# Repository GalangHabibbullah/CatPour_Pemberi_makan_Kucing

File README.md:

# 🐱 **CatPour** 🐱

---
🐱CatPour🐱 - SOLUSI CERDAS PARA CATLOVERS
Pernah merasa bersalah karena lupa memberi makan kucing karena sedang bepergian jauh? Atau bingung berapa porsi makan kucing yang dibutuhkan? CatPour hadir sebagai solusi cerdas para catlovers

Bayangkan kamu pulang ke rumah setelah berlibur. Kucingmu mengeong karena sedang kelaparan karena makanan yang telah kamu siapkan sudah habis tak bersisa. Tapi tenang kejadian itu tidak akan terulang ketika CatPour hadir.

CatPour hadir untuk menyelesaikan masalah para catlovers ketika sedeang bepergian. Sekarang Catlovers tidak perlu khawatir terhadap kucing piaraanya yang kelaparan, karena Catpour memberikan makanan secara otomatis sesuai jadwal dan dalam porsi yang cukup.

---
## 🎬 Commercial Video

---
## BUKU PANDUAN
📘 [Klik di sini untuk melihat buku proyek](./ASSET/buku.pdf)

## Link simulasi Wokwi
-- https://wokwi.com/projects/432622796153693185
-- [https://github.com/GalangHabibbullah/CatPour_Pemberi_makan_Kucing/tree/fe5401d0f07f7c271f16389e5ba98aa213cf10a5/PROGRAM/Wokwi](https://github.com/GalangHabibbullah/CatPour_Pemberi_makan_Kucing/issues/2#issue-3108791988)

---

## Link Video Demo
-- [https://github.com/GalangHabibbullah/CatPour_Pemberi_makan_Kucing/tree/d1d1669227759c1687d57a3f496b5af06effbe53/PROGRAM/Demo](https://github.com/GalangHabibbullah/CatPour_Pemberi_makan_Kucing/issues/1#issue-3108780877)

---

## TINGVERS
-- https://www.thingiverse.com/thing:7054144

---

## LINK PPT PRESENTASI

---

## LINK FIGMA
https://www.figma.com/design/loQbXYYag1uOcxZlFO6y6Z/Untitled?node-id=12-356&p=f&t=XrePOnV4dfjZV4aA-0

---
## 🎯 Objectives

- Mendeteksi jumlah sisa makanan pada bak penampungan makan  
- Memberi makan sesuai dengan porsi si kucing
- Memberi makan secara otomatis sesuai dengan jadwal makan.
- Menyediakan monitoring sisa makanan secara real-time melalui UART ke komputer
---
## 🧠 LATAR BELAKANG
Mempunyai kucing piaraan merupakan kesenangan sebagian orang, sering kali juga menjadi tantangan dalam hal pemberian makan, terutama bagi orang-orang sibuk atau yang sering  bepergian. Salah satu penyebab ketidakaturan ini bisa berdampak pada kesehatan kucing

**CatPour** memberikan solusi dengan cara pemberian makan otomatis sesuai porsi makan kucing  yang dibutuhkan.

---

## 🦾 Support BY :
>- Dosen Pengampu : Akhmad Hendriawan ST., MT. (NIP.197501272002121003)<br>
>- Mata kuliah : Workshop Mikrokontroller<br>
>- Program Studi : D3 Teknik Elektronika<br>
>- Politeknik Elektronika Negeri Surabaya<br>
---
## 😎 Team Member
|      NRP      |        Nama       |        Jobdesk        |                    Akun                  |
| :-----------: |:----------------: | :-------------------: | :---------------------------------------:|
| 2123500004    | Rachmat Dhani G   | 3D Design             | [Dhani](https://github.com/rachmatdhani)
| 2123500005    | M. Ghibran K      | Hardware              | [Ghibran](https://github.com/Smolyyymokka)
| 2123500020    | Adhitya Ramadhani | UI / UX Design        | [Firman](https://github.com/adhitya161004)
| 2123500025    | Adhi Pramana R    | Programmer            | [Rama](https://github.com/Adhi-Rama)
| 2123500030    | Galang Habibbullah| Project Manager       | [Galang](https://github.com/GalangHabibbullah)
---
## 🔗 KOMPONEN 🔗 

Proyek ini mengembangkan sistem pemberian makan kucing otomatis berbasis IoT menggunakan komponen utama seperti **Arduino Uno**, **RTC (Real-Time Clock)**, **Loadcell**, dan **sensor HC-SR04**. 
| Komponen        | Fungsi                                                                                   |
|-----------------|------------------------------------------------------------------------------------------|
| **Arduino Uno** | Berfungsi sebagai mikrokontroler utama yang mengontrol sistem, komunikasi sensor, dan pengaturan pemberian makan otomatis. |
| **RTC**         | Menjaga sinkronisasi waktu untuk pemberian makan sesuai jadwal yang telah diatur.         |
| **Loadcell**    | Mengukur berat makanan di wadah makan untuk memastikan porsi makanan yang tepat.          |
| **Sensor HC-SR04** | Untuk memonitoring jumlah kesediaan ppakan dipenampungan pakan.    |
---
## Desain 3D PCB
Desain 3D VIEW KICAD

---

## Desain Schematic PCB
Desain Schematic 

---
## Desain Layout
Desain Layout PCB 

---
## Desain  PCB JADI
Hasil Cetak PCB

---
## Desain 3D Alat

---
## Desain Jadi

---
## 📊Diagram Blok
Diagram Blok Sistem.

---

## Software Tools

- [Arduino IDE](https://www.arduino.cc/en/software)
- [KiCad](https://kicad.org/)
- [Figma](https://www.figma.com/)
- [Visual Studio Code](https://code.visualstudio.com/)
---
## PRINSIP KERJA 
## Pembacaan penampungan makan
- Sensor HCSR 04 mengirim nilai jarak yang dikonversi menjadi nilai %
100 % = Penampungan Makan Full ; 0 % = Penampungan Makan Kosong
- Sensor Loadcell membaca berat pakan kucing yang keluar, apabila mencapai 20 gram maka servo akan menutup
## Pemrosesan oleh Arduino 
- Arduino  Membaca data  sensor secara berkala, Keputusan diambil untuk membuka servo atau menutup servo
## Tampilan Gui 
- GUI akan menampilkan data berat, sisa makan dan juga posisi servo

--- 
## Pengembangan Kedepannya
- Penambahan Kamera untuk pemantauan jarak jauh
- Penambahan Pemberi minum secara otomatis

---
## 📫 Contact Information

untuk segala informasi, kolaborasi, dan juga pemesanan alat bisa kirim email dibawah ini

**📧 Email:** galanghabibbullah3@gmail.com)

Hanya aktif saat jam kerja, berikan subjek pada email agar  dibalas lebih cepat

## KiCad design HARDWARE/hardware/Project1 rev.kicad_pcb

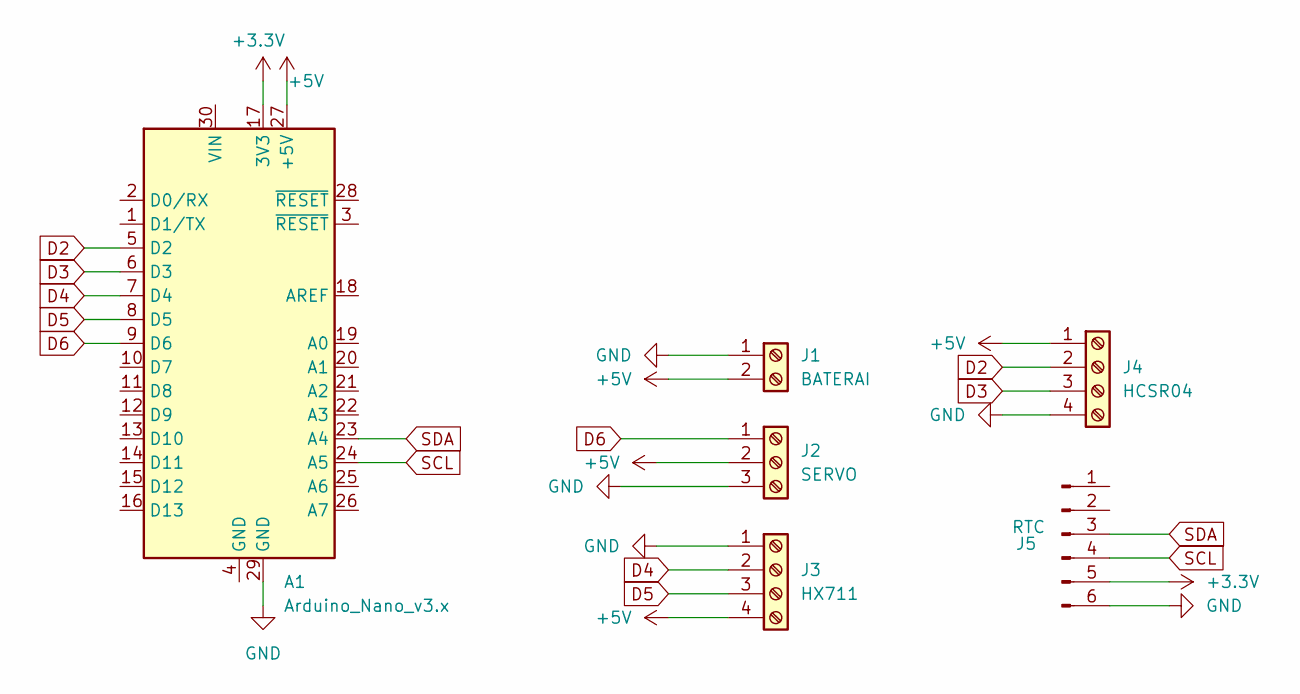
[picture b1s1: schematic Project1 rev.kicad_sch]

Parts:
A1: Arduino_Nano_v3.x; Arduino_Nano
J1: BATERAI; TerminalBlock_Phoenix_PT-1,5-2-5.0-H_1x02_P5.00mm_Horizontal
J2: SERVO; TerminalBlock_Phoenix_PT-1,5-3-5.0-H_1x03_P5.00mm_Horizontal
J3: HX711; TerminalBlock_Phoenix_PT-1,5-4-5.0-H_1x04_P5.00mm_Horizontal
J4: HCSR04; TerminalBlock_Phoenix_PT-1,5-4-5.0-H_1x04_P5.00mm_Horizontal
J5: RTC; PinSocket_1x06_P2.54mm_Vertical

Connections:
+3.3V: A1.17 (3V3), J5.5
+5V: A1.27 (+5V), J1.2, J2.2, J3.4, J4.1
D2: A1.5 (D2), J4.2
D3: A1.6 (D3), J4.3
D4: A1.7 (D4), J3.2
D5: A1.8 (D5), J3.3
D6: A1.9 (D6), J2.1
GND: A1.29 (GND), J1.1, J2.3, J3.1, J4.4, J5.6
SCL: A1.24 (A5), J5.4
SDA: A1.23 (A4), J5.3

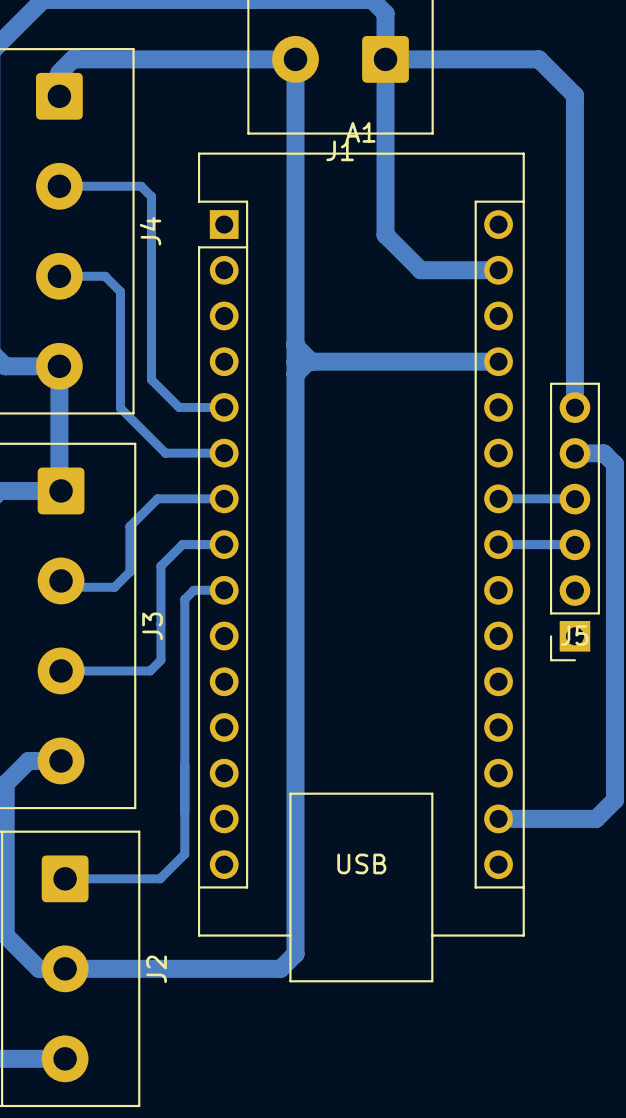
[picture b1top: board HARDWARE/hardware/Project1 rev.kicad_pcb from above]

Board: 2 copper layers, 6 parts (0 on the bottom side), 10 nets.

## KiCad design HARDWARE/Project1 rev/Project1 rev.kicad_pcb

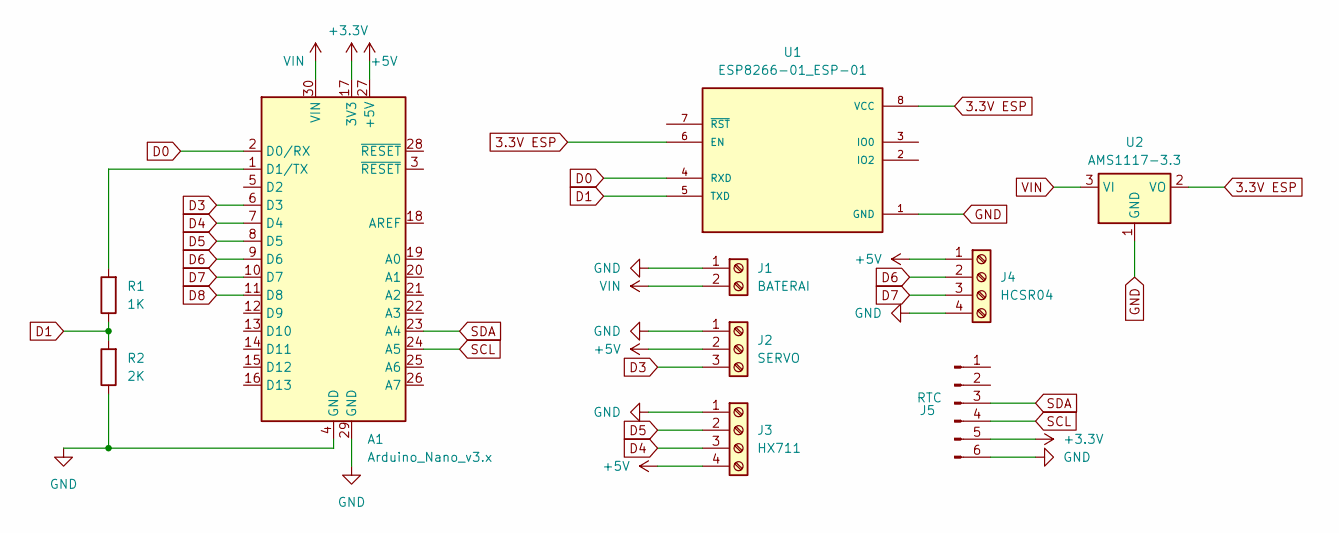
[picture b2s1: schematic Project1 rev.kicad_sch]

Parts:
A1: Arduino_Nano_v3.x; Arduino_Nano
J1: BATERAI; TerminalBlock_4Ucon_1x02_P3.50mm_Horizontal
J2: SERVO; TerminalBlock_4Ucon_1x03_P3.50mm_Vertical
J3: HX711; TerminalBlock_4Ucon_1x04_P3.50mm_Vertical
J4: HCSR04; TerminalBlock_4Ucon_1x04_P3.50mm_Vertical
J5: RTC; PinSocket_1x06_P2.54mm_Vertical
R1: 1K; R_Axial_DIN0207_L6.3mm_D2.5mm_P7.62mm_Horizontal
R2: 2K; R_Axial_DIN0207_L6.3mm_D2.5mm_P7.62mm_Horizontal
U1: ESP8266-01_ESP-01; XCVR_ESP8266-01_ESP-01; PARTREV V1.2
U2: AMS1117-3.3; SOT-223-3_TabPin2

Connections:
3.3V ESP: U1.6 (EN), U1.8 (VCC), U2.2 (VO)
+3.3V: A1.17 (3V3), J5.5
+5V: A1.27 (+5V), J2.2, J3.4, J4.1
D0: A1.2 (D0/RX), U1.4 (RXD)
D1: R1.1, R2.2, U1.5 (TXD)
D3: A1.6 (D3), J2.3
D4: A1.7 (D4), J3.3
D5: A1.8 (D5), J3.2
D6: A1.9 (D6), J4.2
D7: A1.10 (D7), J4.3
D8: A1.11 (D8)
GND: A1.4 (GND), A1.29 (GND), J1.1, J2.1, J3.1, J4.4, J5.6, R2.1, U1.1 (GND), U2.1 (GND)
unnamed: A1.1 (D1/TX), R1.2
SCL: A1.24 (A5), J5.4
SDA: A1.23 (A4), J5.3
VIN: A1.30 (VIN), J1.2, U2.3 (VI)

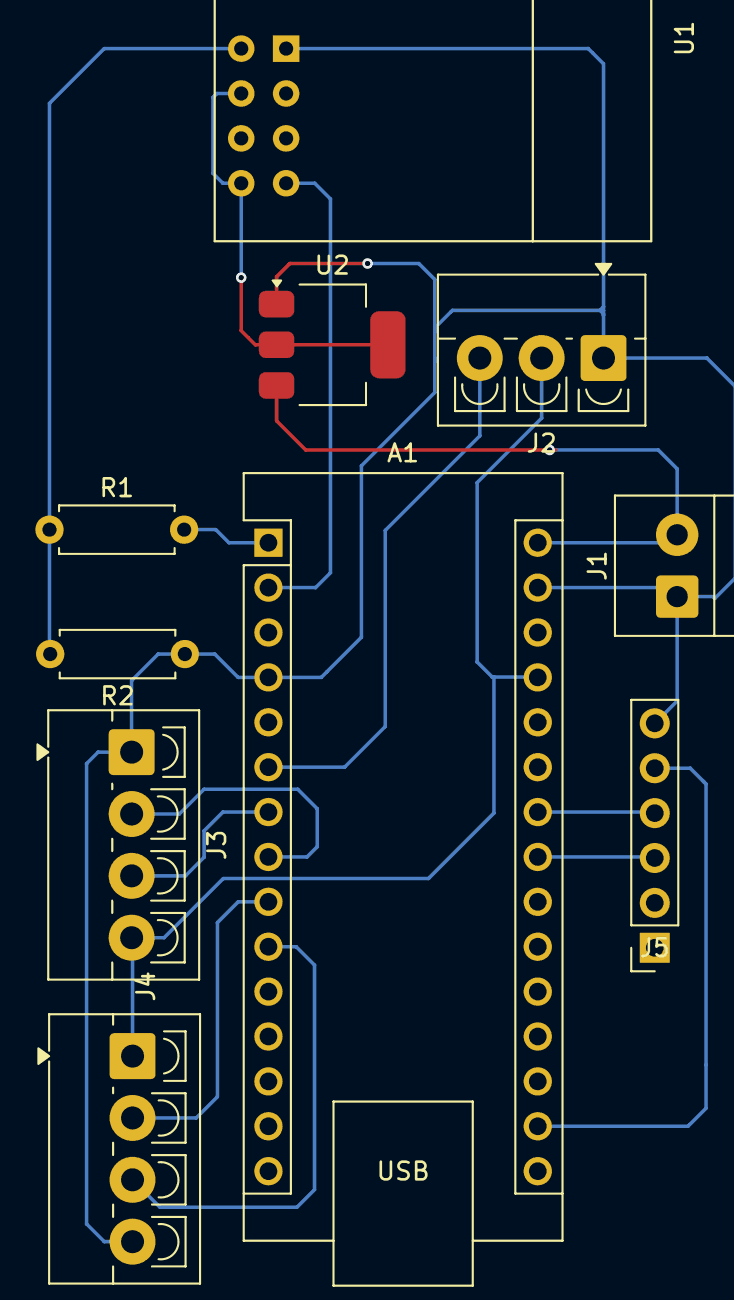
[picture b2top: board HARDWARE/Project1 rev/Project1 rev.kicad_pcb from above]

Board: 2 copper layers, 10 parts (0 on the bottom side), 15 nets.

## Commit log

2025-04-26 Create assets
2025-04-26 update terbaru
2025-04-26 Menambahkan .gitkeep di semua folder kosong
2025-05-04 Pesan commit kamu di sini
2025-05-25 Menambahkan folder hardware
